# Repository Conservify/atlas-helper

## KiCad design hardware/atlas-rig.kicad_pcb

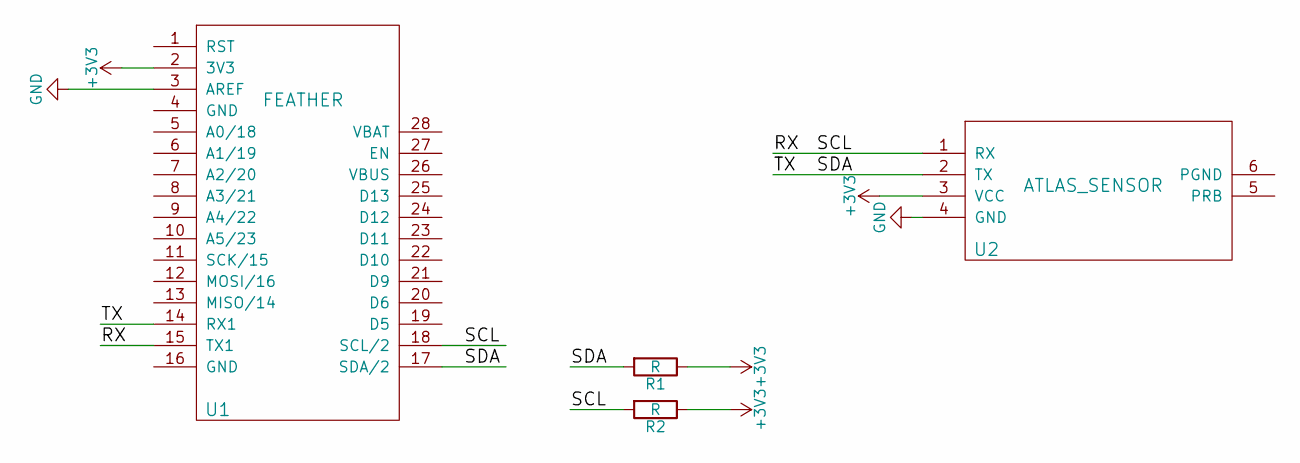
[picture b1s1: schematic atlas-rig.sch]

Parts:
R1, R2: R; R_Axial_DIN0309_L9.0mm_D3.2mm_P15.24mm_Horizontal
U1: FEATHER; feather
U2: ATLAS_SENSOR; atlas_sensor_board

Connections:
+3V3: R1.1, R2.1, U1.2 (3V3), U2.3 (VCC)
/RX: R2.2, U1.15 (TX1), U1.18 (SCL/2), U2.1 (RX)
/SDA: R1.2, U1.14 (RX1), U1.17 (SDA/2), U2.2 (TX)
GND: U1.3 (AREF), U2.4 (GND)

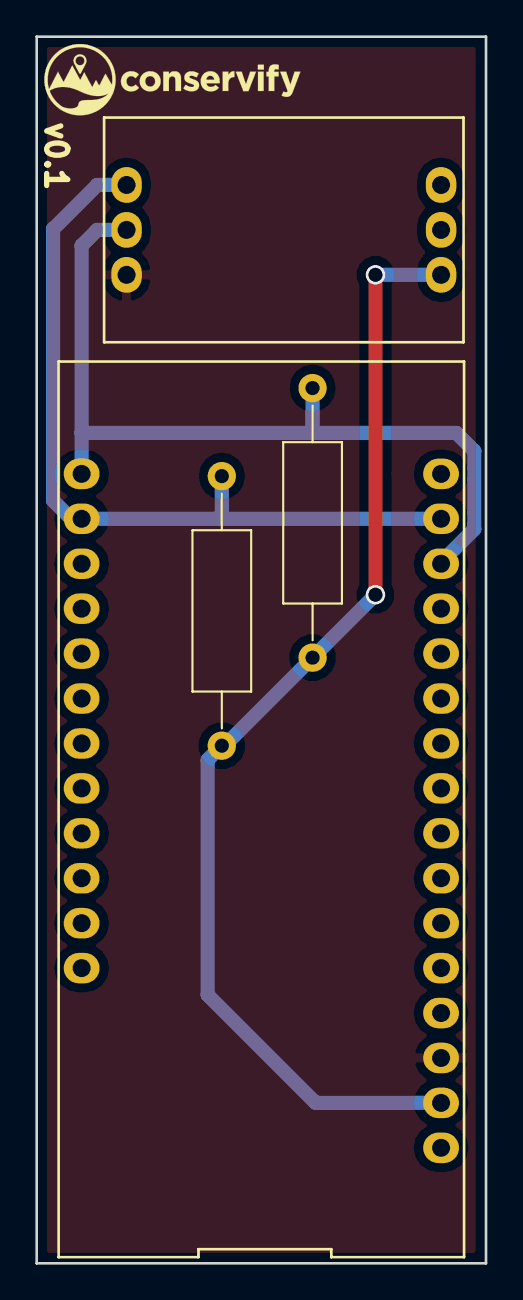
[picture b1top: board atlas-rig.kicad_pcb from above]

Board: 2 copper layers, 25.4 x 69.3 mm, 4 parts (0 on the bottom side), 4 nets.

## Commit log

2017-11-03 First commit.
2017-12-20 Rename to main.cpp More aggressive I2C finding.
2017-12-20 Blank readme.
2017-12-21 Some PCB tweaks, nothing major.
2018-01-11 Use LED as indicator. Only wait 2s for serial.
2018-04-20 Firmware updates to actuall lock protocols.
2018-04-20 Move Makefile up.
2018-04-20 Fix paths to CMake and Arduino stuff.
2018-07-18 Can leave this running now.
2019-05-30 Use newer Arduino cmake stuff.
